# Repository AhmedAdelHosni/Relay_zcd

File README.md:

UPDATE 19.12.2018:
- Tested today the relay with Arduino UNO on pin 2 which is configured with PULL UP resistor. The circuit worked very good and the capacitor successfully reported only LOW as long as the AC light is ON, and HIGH as long as the AC is OFF. 

TODO: Test the circuit with long wiring more than 25 meters and put the capacitor near the controller itself and monitor the performance.
The above TODO has been verified successfully

# Relay_zcd
Relay circuit to control a relay and detect the status of the AC switch using SFH620A optocoupler. 
The idea is to be used in a Smart House to be able to connect the relay with a 3 way switch. It is important to detect the light state so that the application can decide whether to turn off or on the relay. 
The optocoupler is normally pulled to HIGH and goes LOW when the AC is rising which turns on the LED in the optocoupler. When the LED is ON the transistor in the SFH620A will connect the output Signal to GND.
Normally the pin wil be low for ~9ms and high for ~1ms. To avoid this pulsing the idea is to add a capacitor with value 0.1uF to delay the rising of the pin to HIGH when the AC is at zero crossing detection.

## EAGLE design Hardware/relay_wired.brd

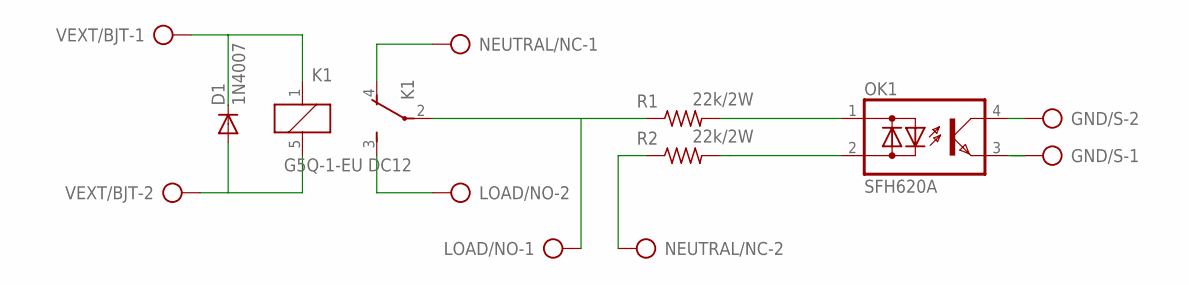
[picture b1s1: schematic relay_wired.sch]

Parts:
D1: 1N4007; D-5
GND/S: AK500/2
K1: G5Q-1-EU DC12; G5SB
LOAD/NO: AK500/2
NEUTRAL/NC: AK500/2
OK1: SFH620A; DIL04
R1, R2: 22k/2W; 0207/12
VEXT/BJT: AK500/2

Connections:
unnamed: OK1.2 (AC2), R2.2
unnamed: OK1.1 (AC1), R1.2
unnamed: GND/S.2, OK1.4 (C)
unnamed: NEUTRAL/NC.2, R2.1
unnamed: GND/S.1, OK1.3 (E)
unnamed: K1.3 (S), LOAD/NO.2
unnamed: D1.C, K1.1, VEXT/BJT.1
unnamed: D1.A, K1.5 (2), VEXT/BJT.2
unnamed: K1.2, LOAD/NO.1, R1.1
unnamed: K1.4 (O), NEUTRAL/NC.1

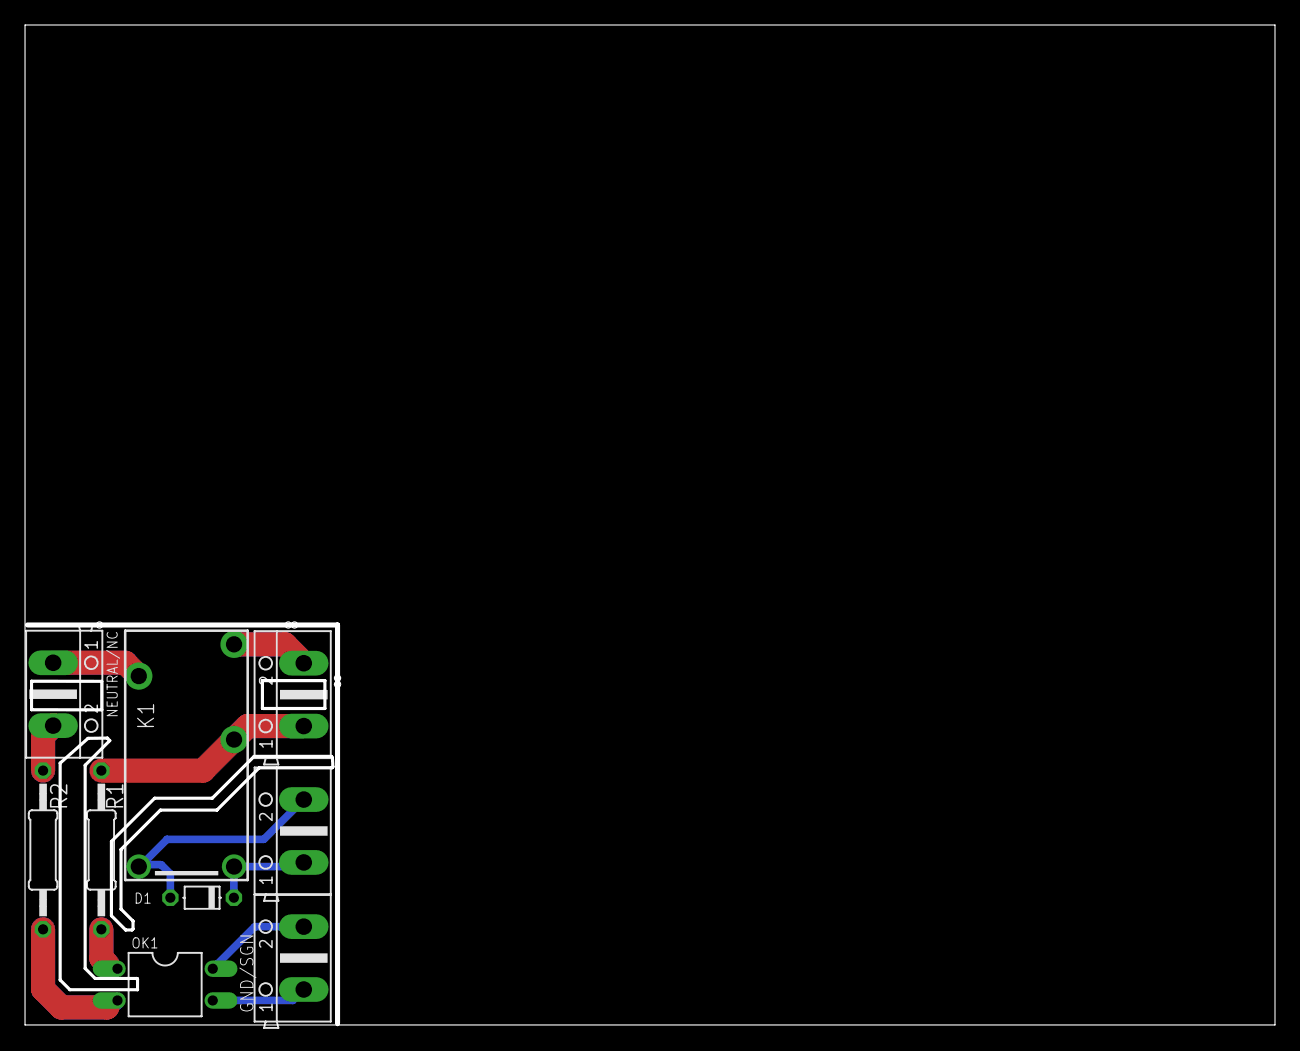
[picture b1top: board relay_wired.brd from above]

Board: 2 copper layers, 99.6 x 79.7 mm, 9 parts (0 on the bottom side), 10 nets.

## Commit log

2018-11-24 :octocat: Added .gitattributes & .gitignore files
2018-11-24 Create Schematics
    First commit, created schematics for turning ON/OFF a relay + detecting
    the status of the Relay using a bridge rectifier and an opto coupler.
    Circuit not tested yet and passive values are not defined.
2018-11-26 Layout of board 33 x 33
    Layout 33 x 33 board
2018-12-06 Change layout to 25x40mm
    - Change the layout to 25x40 mm since the max board size in the free eagle version is 160mm2 (100x80)
    - Added text on pcb board layout and fixed trace width
2018-12-15 Branch for new design using SFH620A
    Due to design layout size limitation - after fixing parts size - it was not possible to fit in the 25x40 layout a pc817 and a DB107 for detecting zero crossing. Thus this branch is to replace both wi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
    - Changed the terminal block size from 2.54 mm to 5 mm pith instead since this was available in the market.
    - Changed the relay to SONGLE SRD-05VDC-SL-C design. Library is added also
    - Changed resistors value to 0207/12 to fit 22k / 1W resistor value.
    - Changed pic817 and DB107 with SFH620A
    - reroute pcb layout again.
2018-12-19 Invert NC and NO name tags
    Changes in schematic.
2019-01-20 Branching for Omron G5Q-1-EU DC12 relay
    - Replaced relay to Omron G5Q-1-EU DC12
    - Board size reduced from 40x25 to 32x25
2019-01-20 [BUG] Relay was set to mirror by mistake
    - A major bug while reviewing where the relay was set to mirror.
    - Updated gerb274x.cam to generate silk screen for bottom also
2019-01-24 Routing and creepage
    - Routed the circuit
    - Added creepage as lines not polygon
    - Review is done. Shall be a stable version but not tested yet.
2019-02-10 Add some creepage
